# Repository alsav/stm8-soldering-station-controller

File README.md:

Tomizawa FZ-880B soldering station controller open-source firmware
==================================================================

Цель данного проекта - реанимация умершего чуда китайской инженерной мысли: паяльника с терморегуляцией Tomizawa FZ-880 и его клонов.
Т.к. схемотехника агрегата мягко говоря не очень, возможно еще кому-то пригодится...

Итак, самое слабое место - схема питания МК. Если паяльник перестал подавать признаки жизни и при включении в розетку монотонно горят один илн несколько светодиодов - ваш случай.

Для восстановления потребуется:
1. Прокачать до второго уровня или выше схему питания микроконтроллера (см.фото).
2. Изготовить методом лута печатку под новый МК STM8S003F3P6, прикупив последний где-нибудь тут: http://www.ebay.com/sch/i.html?&_nkw=stm8s003f3
3. Прошить МК и установить плату вместо стокового контроллера на свободное место.

Файлы:
1. firmware_vX.X.hex - сама прошивка.
2. ctrl-brd_reduced-F_Cu.ps - шаблон для изготовления платы (формат post-script).
3. Все остальное - если будете заморачиваться с допилкой под сови нужды и повторной сборкой.

Для компиляции использовался sdcc 3.4.3 #9179 под linux (ubuntu 14.04).
Для шитья - Versaloon (в проекте) или более доступное средство: ST_Link V2.

Features:
1. Термостабилизация ПИД-регулятором. Точность 5-10С.
2. Предварительный прогрев до температуры режима n+1 для сокращения времени нагрева жала.
3. Индикация выхода на рабочий температурный режим миганием светодиода.
4. Отключение паяла длинным нажатием.

TODO (если будет не лень):
1. Режим калибровки: точная подстройка температуры с сохранением в eeprom.

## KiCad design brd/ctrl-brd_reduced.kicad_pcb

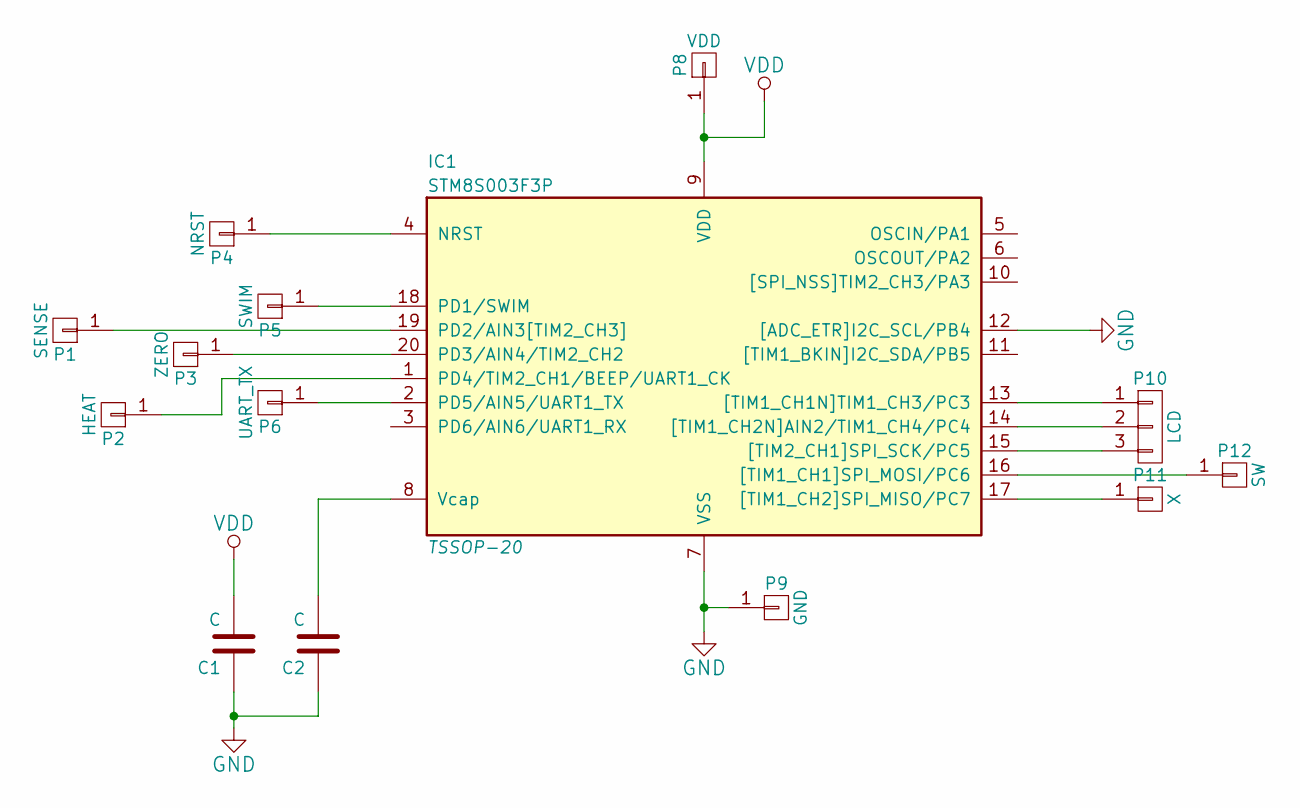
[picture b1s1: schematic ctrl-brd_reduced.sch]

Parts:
C1, C2: C
IC1: STM8S003F3P; TSSOP-20
P1: SENSE
P2: HEAT
P3: ZERO
P4: NRST
P5: SWIM
P6: UART_TX
P8: VDD
P9: GND
P10: LCD
P11: X
P12: SW

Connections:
GND: C1.1, C2.1, IC1.7 (VSS), IC1.12 ([ADC_ETR]I2C_SCL/PB4), P9.1
unnamed: IC1.15 ([TIM2_CH1]SPI_SCK/PC5), P10.3
unnamed: IC1.14 ([TIM1_CH2N]AIN2/TIM1_CH4/PC4), P10.2
unnamed: IC1.13 ([TIM1_CH1N]TIM1_CH3/PC3), P10.1
unnamed: IC1.18 (PD1/SWIM), P5.1
unnamed: C2.2, IC1.8 (Vcap)
unnamed: IC1.4 (NRST), P4.1
unnamed: IC1.1 (PD4/TIM2_CH1/BEEP/UART1_CK), P2.1
unnamed: IC1.19 (PD2/AIN3[TIM2_CH3]), P1.1
unnamed: IC1.16 ([TIM1_CH1]SPI_MOSI/PC6), P12.1
unnamed: IC1.17 ([TIM1_CH2]SPI_MISO/PC7), P11.1
unnamed: IC1.20 (PD3/AIN4/TIM2_CH2), P3.1
unnamed: IC1.2 (PD5/AIN5/UART1_TX), P6.1
VDD: C1.2, IC1.9 (VDD), P8.1

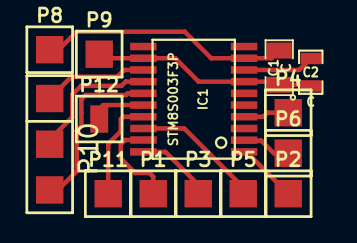
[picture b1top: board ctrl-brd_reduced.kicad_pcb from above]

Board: 2 copper layers, 14 parts (0 on the bottom side), 14 nets.

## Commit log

2015-03-06 INIT!
2015-03-06 Some cleanups
2015-03-09 Beta 1.0
2015-03-10 big cleanup
2015-03-10 More clean and more readable code. Added copyright and about info.
2015-03-10 Added ST licence to ministdlib.c
2015-03-15 Changed preheat and poweroff-timer limits. Ver 0.2
2015-07-12 Added docs for Issue #1
